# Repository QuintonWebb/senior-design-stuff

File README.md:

# senior-design-stuff
Just a place to put senior design. Will add explain later.

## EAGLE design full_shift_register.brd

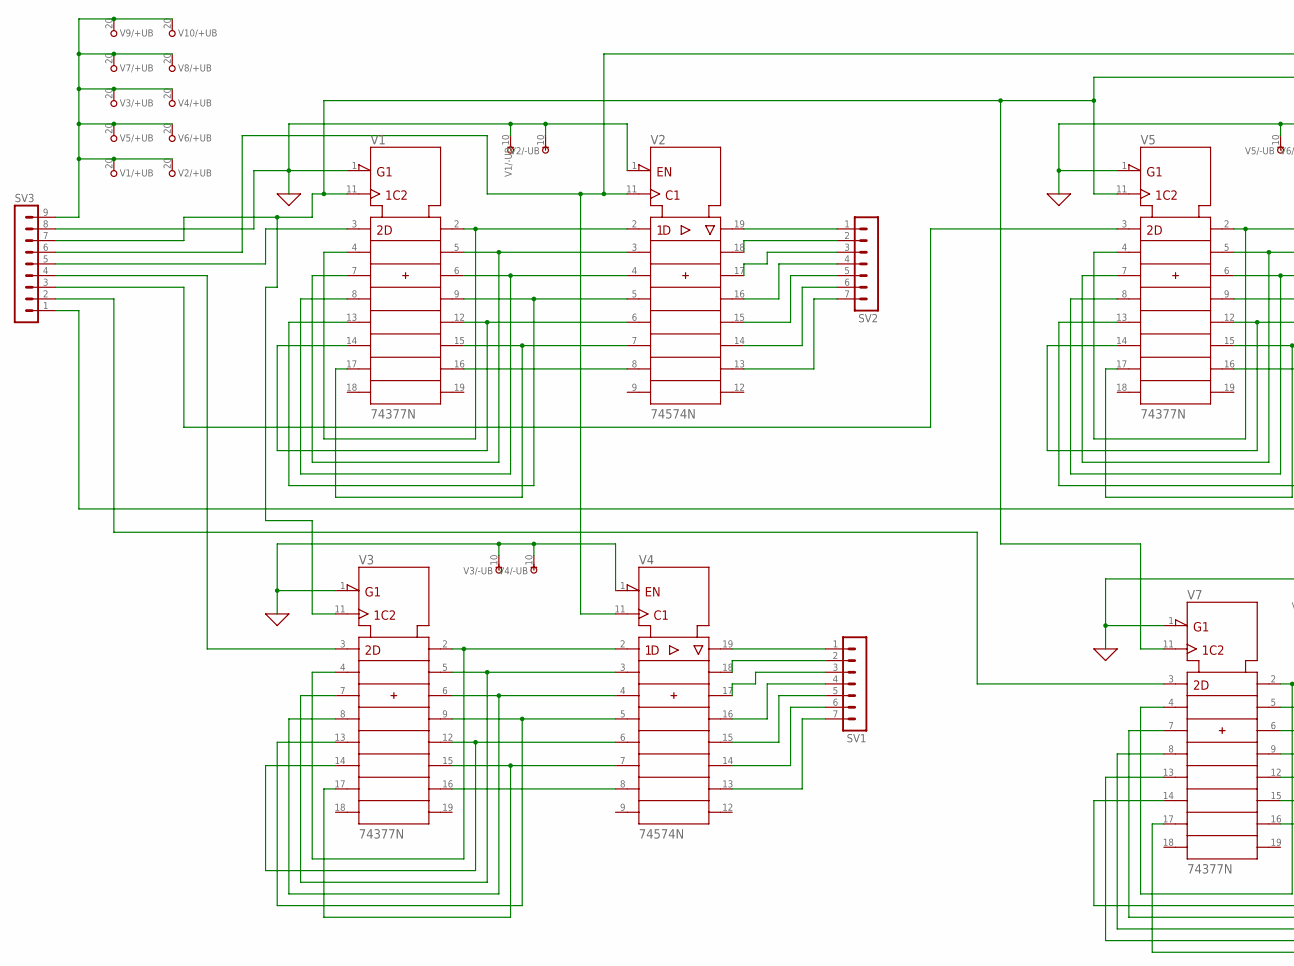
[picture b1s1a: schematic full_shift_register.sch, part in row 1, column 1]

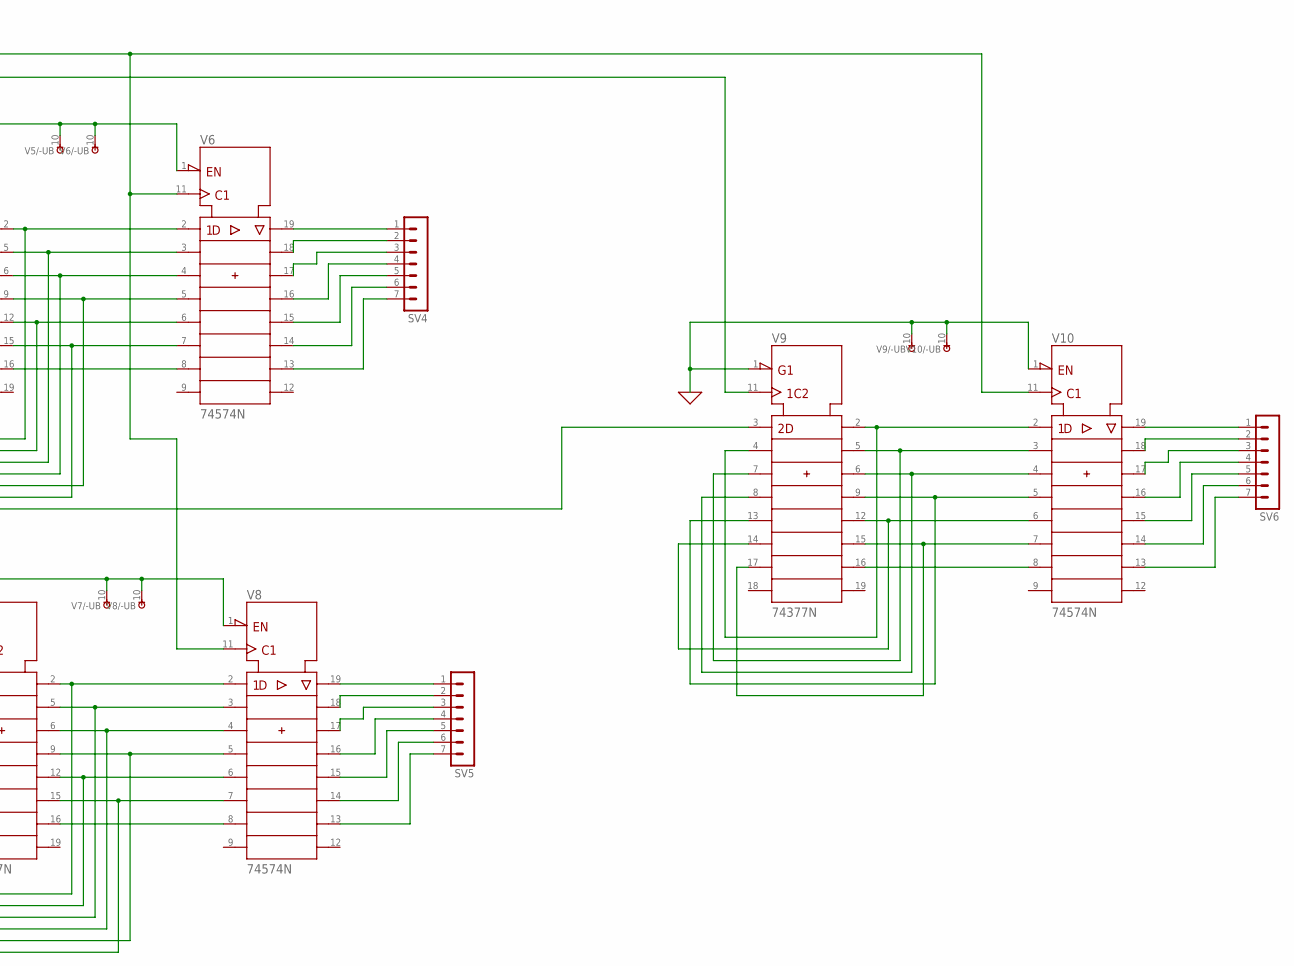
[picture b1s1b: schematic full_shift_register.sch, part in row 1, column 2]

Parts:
SV1, SV2, SV4, SV5, SV6: MA07-1
SV3: MA09-1
V1, V3, V5, V7, V9: 74377N; DIL20
V2, V4, V6, V8, V10: 74574N; DIL20

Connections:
0: SV3.8, V1.1 (!G), V1.10 (-UB), V2.1 (!OC), V2.10 (-UB), V3.1 (!G), V3.10 (-UB), V4.1 (!OC), V4.10 (-UB), V5.1 (!G), V5.10 (-UB), V6.1 (!OC), V6.10 (-UB), V7.1 (!G), V7.10 (-UB), V8.1 (!OC), V8.10 (-UB), V9.1 (!G), V9.10 (-UB), V10.1 (!OC), V10.10 (-UB)
unnamed: V1.2 (1Q), V1.4 (2D), V2.2 (1D)
unnamed: V1.5 (2Q), V1.7 (3D), V2.3 (2D)
unnamed: V1.6 (3Q), V1.8 (4D), V2.4 (3D)
unnamed: V1.9 (4Q), V1.13 (5D), V2.5 (4D)
unnamed: V1.12 (5Q), V1.14 (6D), V2.6 (5D)
unnamed: V1.15 (6Q), V1.17 (7D), V2.7 (6D)
unnamed: V1.16 (7Q), V2.8 (7D)
unnamed: SV3.6, V2.11 (CLK), V4.11 (CLK), V6.11 (CLK), V8.11 (CLK), V10.11 (CLK)
unnamed: SV3.5, V1.3 (1D)
unnamed: SV2.1, V2.19 (1Q)
unnamed: SV2.2, V2.18 (2Q)
unnamed: SV2.3, V2.17 (3Q)
unnamed: SV2.4, V2.16 (4Q)
unnamed: SV2.5, V2.15 (5Q)
unnamed: SV2.6, V2.14 (6Q)
unnamed: SV2.7, V2.13 (7Q)
unnamed: V3.2 (1Q), V3.4 (2D), V4.2 (1D)
unnamed: V3.5 (2Q), V3.7 (3D), V4.3 (2D)
unnamed: V3.6 (3Q), V3.8 (4D), V4.4 (3D)
unnamed: V3.9 (4Q), V3.13 (5D), V4.5 (4D)
unnamed: V3.12 (5Q), V3.14 (6D), V4.6 (5D)
unnamed: V3.15 (6Q), V3.17 (7D), V4.7 (6D)
unnamed: V3.16 (7Q), V4.8 (7D)
unnamed: SV1.1, V4.19 (1Q)
unnamed: SV1.2, V4.18 (2Q)
unnamed: SV1.3, V4.17 (3Q)
unnamed: SV1.4, V4.16 (4Q)
unnamed: SV1.5, V4.15 (5Q)
unnamed: SV1.6, V4.14 (6Q)
unnamed: SV1.7, V4.13 (7Q)
unnamed: SV3.4, V3.3 (1D)
unnamed: V7.2 (1Q), V7.4 (2D), V8.2 (1D)
unnamed: V7.5 (2Q), V7.7 (3D), V8.3 (2D)
unnamed: V5.2 (1Q), V5.4 (2D), V6.2 (1D)
unnamed: V5.5 (2Q), V5.7 (3D), V6.3 (2D)
unnamed: V5.6 (3Q), V5.8 (4D), V6.4 (3D)
unnamed: V5.9 (4Q), V5.13 (5D), V6.5 (4D)
unnamed: V5.12 (5Q), V5.14 (6D), V6.6 (5D)
unnamed: V5.15 (6Q), V5.17 (7D), V6.7 (6D)
unnamed: V5.16 (7Q), V6.8 (7D)
unnamed: SV4.1, V6.19 (1Q)
unnamed: SV4.2, V6.18 (2Q)
unnamed: SV4.3, V6.17 (3Q)
unnamed: SV4.4, V6.16 (4Q)
unnamed: SV4.5, V6.15 (5Q)
unnamed: SV4.6, V6.14 (6Q)
unnamed: SV4.7, V6.13 (7Q)
unnamed: SV3.3, V5.3 (1D)
unnamed: V7.6 (3Q), V7.8 (4D), V8.4 (3D)
unnamed: V7.9 (4Q), V7.13 (5D), V8.5 (4D)
unnamed: V7.12 (5Q), V7.14 (6D), V8.6 (5D)
unnamed: V7.15 (6Q), V7.17 (7D), V8.7 (6D)
unnamed: V7.16 (7Q), V8.8 (7D)
unnamed: SV5.1, V8.19 (1Q)
unnamed: SV5.2, V8.18 (2Q)
unnamed: SV5.3, V8.17 (3Q)
unnamed: SV5.4, V8.16 (4Q)
unnamed: SV5.5, V8.15 (5Q)
unnamed: SV5.6, V8.14 (6Q)
unnamed: SV5.7, V8.13 (7Q)
unnamed: SV3.2, V7.3 (1D)
unnamed: V9.2 (1Q), V9.4 (2D), V10.2 (1D)
unnamed: V9.5 (2Q), V9.7 (3D), V10.3 (2D)
unnamed: V9.6 (3Q), V9.8 (4D), V10.4 (3D)
unnamed: V9.9 (4Q), V9.13 (5D), V10.5 (4D)
unnamed: V9.12 (5Q), V9.14 (6D), V10.6 (5D)
unnamed: V9.15 (6Q), V9.17 (7D), V10.7 (6D)
unnamed: V9.16 (7Q), V10.8 (7D)
unnamed: SV6.1, V10.19 (1Q)
unnamed: SV6.2, V10.18 (2Q)
unnamed: SV6.3, V10.17 (3Q)
unnamed: SV6.4, V10.16 (4Q)
unnamed: SV6.5, V10.15 (5Q)
unnamed: SV6.6, V10.14 (6Q)
unnamed: SV6.7, V10.13 (7Q)
unnamed: SV3.1, V9.3 (1D)
unnamed: SV3.7, V1.11 (CLK), V3.11 (CLK), V5.11 (CLK), V7.11 (CLK), V9.11 (CLK)
unnamed: SV3.9, V1.20 (+UB), V2.20 (+UB), V3.20 (+UB), V4.20 (+UB), V5.20 (+UB), V6.20 (+UB), V7.20 (+UB), V8.20 (+UB), V9.20 (+UB), V10.20 (+UB)

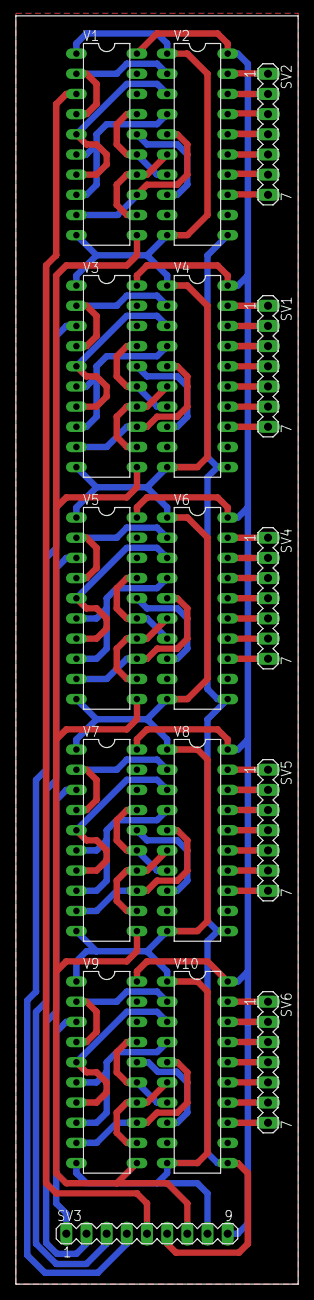
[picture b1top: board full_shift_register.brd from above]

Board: 2 copper layers, 35.5 x 159.7 mm, 16 parts (0 on the bottom side), 79 nets.

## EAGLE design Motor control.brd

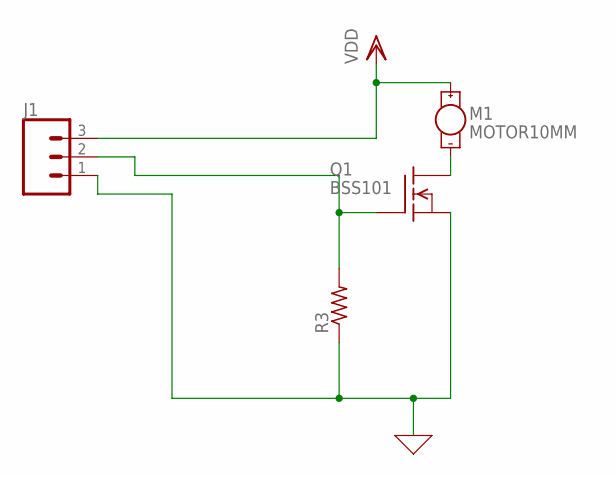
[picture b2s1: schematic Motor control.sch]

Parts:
J1: CONN_03; 1X03
M1: MOTOR10MM; VIBE-MOTOR-10MM
Q1: BSS101; TO92
R3: R-US_0207/10; 0207/10

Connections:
0: J1.1, Q1.1 (S), R3.1
unnamed: M1.-, Q1.3 (D)
unnamed: J1.2, Q1.2 (G), R3.2
VDD: J1.3, M1.+

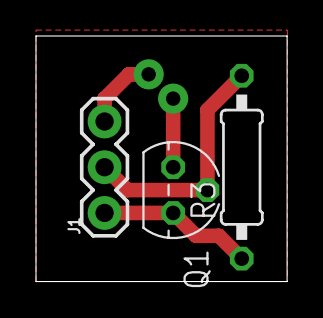
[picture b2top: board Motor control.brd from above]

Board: 2 copper layers, 14.0 x 13.6 mm, 4 parts (1 on the bottom side), 4 nets.

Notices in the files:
parts and their libraries:
SparkFun-Electromechanical: Licensing: Creative Commons ShareAlike 4.0 International - https://creativecommons.org/licenses/by-sa/4.0
